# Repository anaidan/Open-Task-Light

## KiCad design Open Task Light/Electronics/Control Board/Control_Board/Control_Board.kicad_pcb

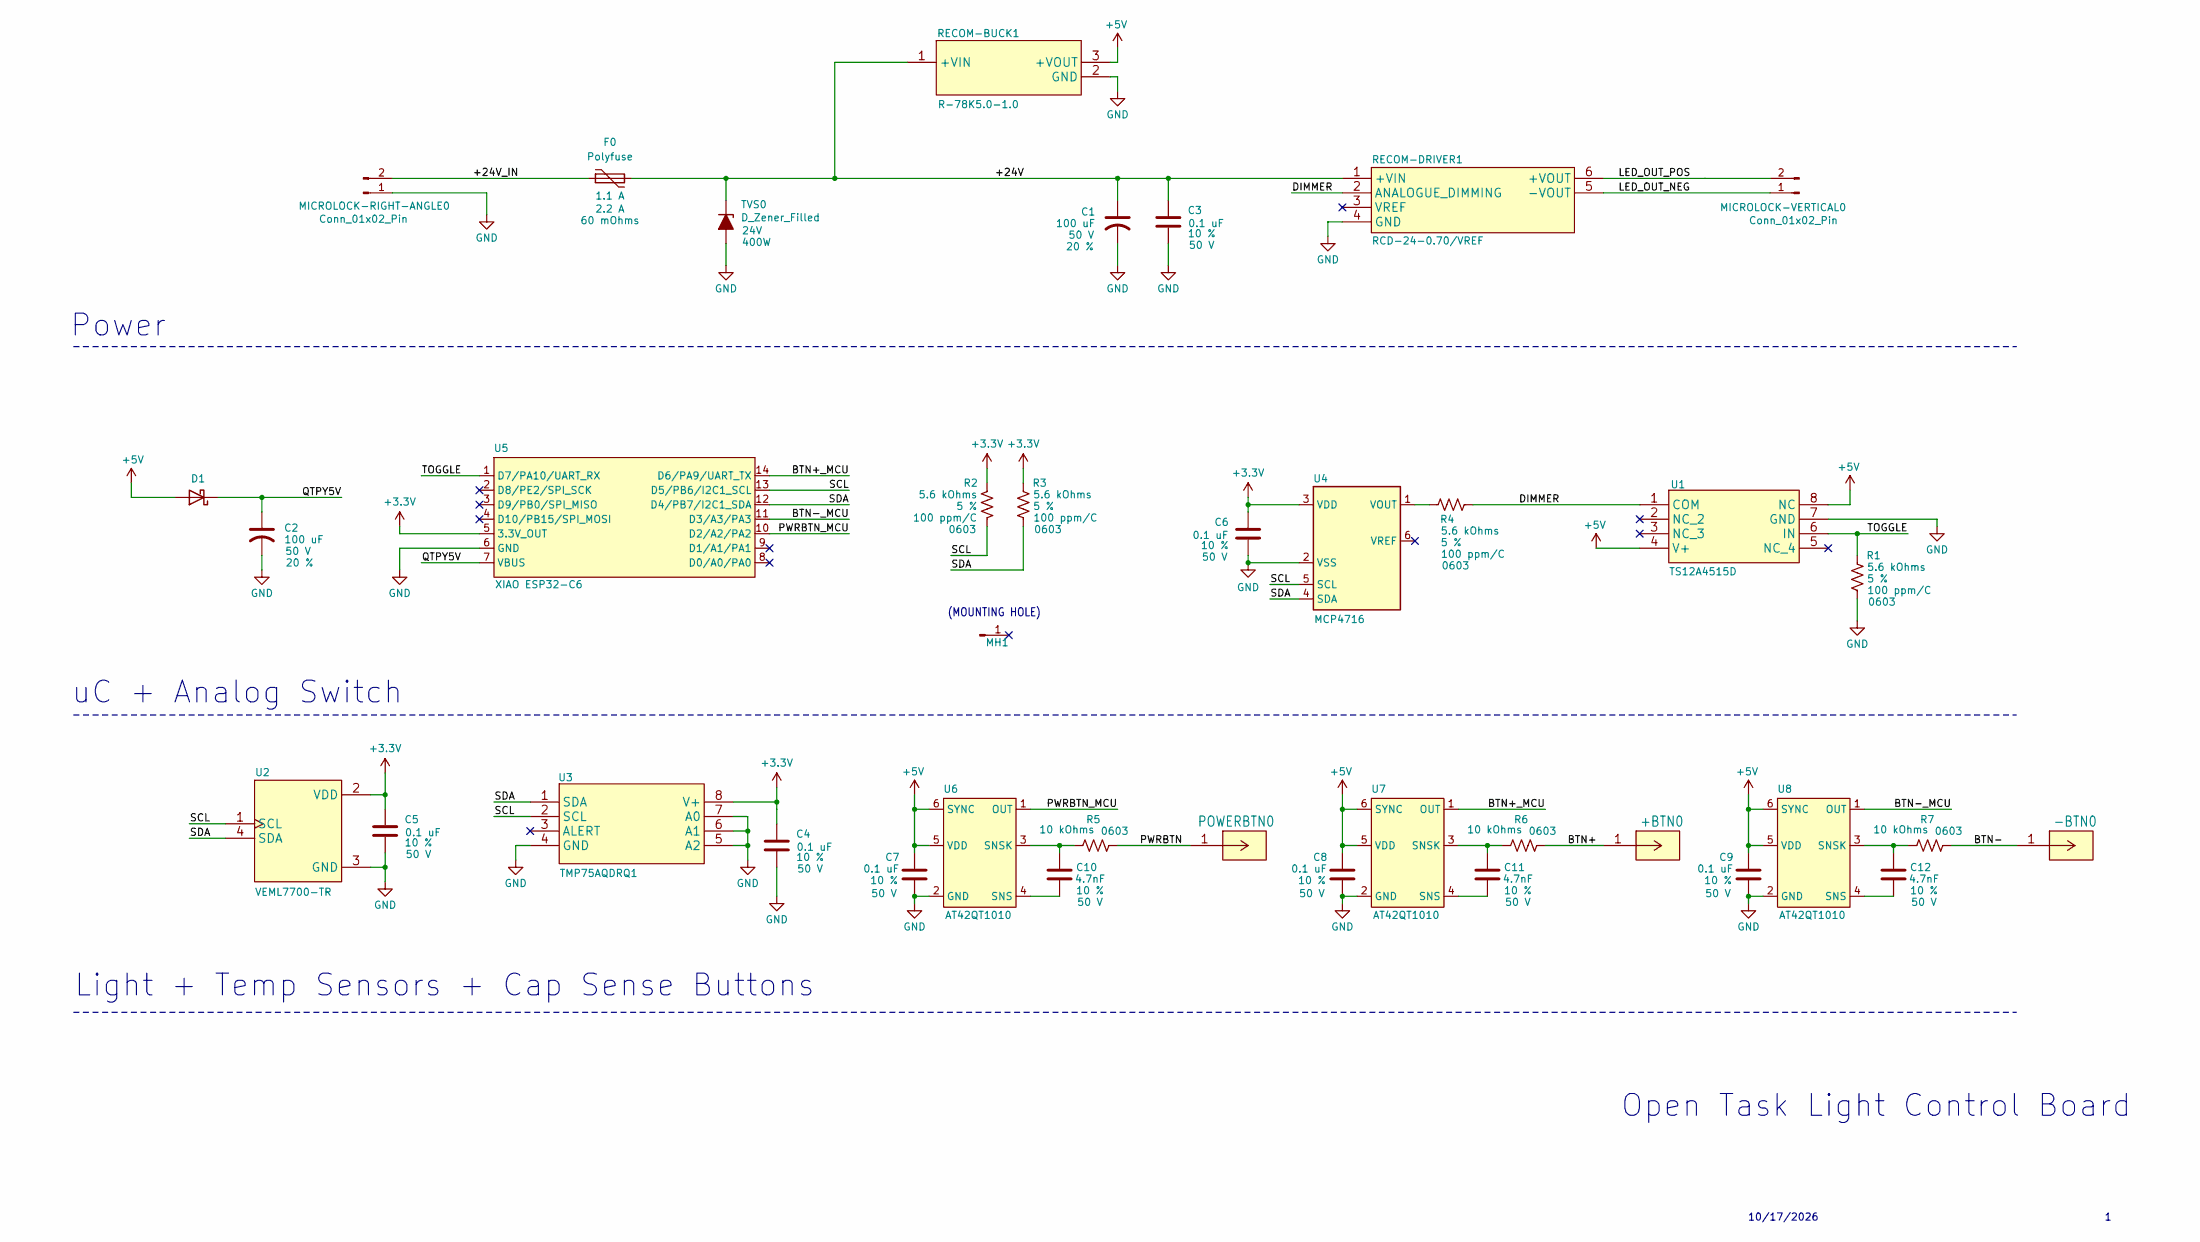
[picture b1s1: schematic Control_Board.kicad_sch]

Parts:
+BTN0: 807-22-001-10-001101; CONN_807-22-001-10-001101_MIM; MPN 807-22-001-10-001101
-BTN0: 807-22-001-10-001101; CONN_807-22-001-10-001101_MIM; MPN 807-22-001-10-001101
C1, C2: EEE-FTH101XAP; CAP_EEEFTH101XAP; Volage Rating 50 V; Tolerance 20 %; MPN EEE-FTH101XAP
C3, C4, C5, C6, C7, C8, C9: C; C_0603_1608Metric; Voltage Rating 50 V; Tolerance 10 %; MPN C0603C104K5RAC9109
C10, C11, C12: C; C_0603_1608Metric; Voltage Rating 50 V; Tolerance 10 %; MPN C0603C472K5RACTU
D1: 1N5819HW-7-F; D_SOD-123; MPN 1N5819HW-7-F
F0: Polyfuse; SMD2016B100TF_33; MPN SMD2016B100TF/33
MH1: 2.5MMPLATEDTHROUGHHOLE; 2.5MMPLATEDHOLE
MICROLOCK-RIGHT-ANGLE0: Conn_01x02_Pin; 2200980271; MPN 2200980271
MICROLOCK-VERTICAL0: Conn_01x02_Pin; 2200970000_A; MPN 2200970271
POWERBTN0: 807-22-001-10-001101; CONN_807-22-001-10-001101_MIM; MPN 807-22-001-10-001101
R1, R2, R3, R4: R_US; R_0603_1608Metric; Tolerance 5 %; MPN AC0603JR-075K6L
R5, R6, R7: R_US; R_0603_1608Metric; Tolerance 5 %; MPN RC0603JR-0710KL
RECOM-BUCK1: R-78K5.0-1.0; R-78K5.0-1.0_RCP; MPN R-78K5.0-1.0
RECOM-DRIVER1: RCD-24-0.70/VREF; RCD24030; MPN RCD-24-0.70/Vref
TVS0: D_Zener_Filled; SODFL3619X98N; MPN SMF4L24AT1G
U1: TS12A4515D; D8-L; MPN TS12A4515D
U2: VEML7700-TR; XDCR_VEML7700-TR; MPN VEML7700-TR
U3: TMP75AQDRQ1; D8_TEX; MPN TMP75AQDRQ1
U4: MCP4716; SOT-23-6; MPN MCP4716A3T-E/CH
U5: XIAO ESP32-C6; ESP32_C6; MPN 113991254
U6, U7, U8: AT42QT1010; SOT-23-6; MPN AT42QT1010-TSHR

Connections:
+3.3V: C4.1, C5.1, C6.1, R2.1, R3.1, U2.2 (VDD), U3.8 (V+), U4.3 (VDD), U5.5 (3.3V_OUT)
+5V: C7.1, C8.1, C9.1, D1.2 (A), RECOM-BUCK1.3 (+VOUT), U1.4 (V+), U1.8 (NC), U6.5 (VDD), U6.6 (SYNC), U7.5 (VDD), U7.6 (SYNC), U8.5 (VDD), U8.6 (SYNC)
/+24V: C1.1, C3.1, F0.2, RECOM-BUCK1.1 (+VIN), RECOM-DRIVER1.1 (+VIN), TVS0.1 (K)
/+24V_IN: F0.1, MICROLOCK-RIGHT-ANGLE0.2
/BTN+: +BTN0.1 (1_1), R6.2
/BTN+_MCU: U5.14 (D6/PA9/UART_TX), U7.1 (OUT)
/BTN-: -BTN0.1 (1_1), R7.2
/BTN-_MCU: U5.11 (D3/A3/PA3), U8.1 (OUT)
/DIMMER: R4.2, RECOM-DRIVER1.2 (ANALOGUE_DIMMING), U1.1 (COM)
/LED_OUT_NEG: MICROLOCK-VERTICAL0.1, RECOM-DRIVER1.5 (-VOUT)
/LED_OUT_POS: MICROLOCK-VERTICAL0.2, RECOM-DRIVER1.6 (+VOUT)
/PWRBTN: POWERBTN0.1 (1_1), R5.2
/PWRBTN_MCU: U5.10 (D2/A2/PA2), U6.1 (OUT)
/QTPY5V: C2.1, D1.1 (K), U5.7 (VBUS)
/SCL: R2.2, U2.1 (SCL), U3.2 (SCL), U4.5 (SCL), U5.13 (D5/PB6/I2C1_SCL)
/SDA: R3.2, U2.4 (SDA), U3.1 (SDA), U4.4 (SDA), U5.12 (D4/PB7/I2C1_SDA)
/TOGGLE: R1.1, U1.6 (IN), U5.1 (D7/PA10/UART_RX)
GND: C1.2, C2.2, C3.2, C4.2, C5.2, C6.2, C7.2, C8.2, C9.2, MICROLOCK-RIGHT-ANGLE0.1, R1.2, RECOM-BUCK1.2 (GND), RECOM-DRIVER1.4 (GND), TVS0.2 (A), U1.7 (GND), U2.3 (GND), U3.4 (GND), U3.5 (A2), U3.6 (A1), U3.7 (A0), U4.2 (VSS), U5.6 (GND), U6.2 (GND), U7.2 (GND), U8.2 (GND)
unnamed: R4.1, U4.1 (VOUT)
unnamed: C10.2, U6.4 (SNS)
unnamed: C10.1, R5.1, U6.3 (SNSK)
unnamed: C11.2, U7.4 (SNS)
unnamed: C11.1, R6.1, U7.3 (SNSK)
unnamed: C12.2, U8.4 (SNS)
unnamed: C12.1, R7.1, U8.3 (SNSK)

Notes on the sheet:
uC + Analog Switch
Power
Open Task Light Control Board
Light + Temp Sensors + Cap Sense Buttons
(MOUNTING HOLE)
10/17/2026

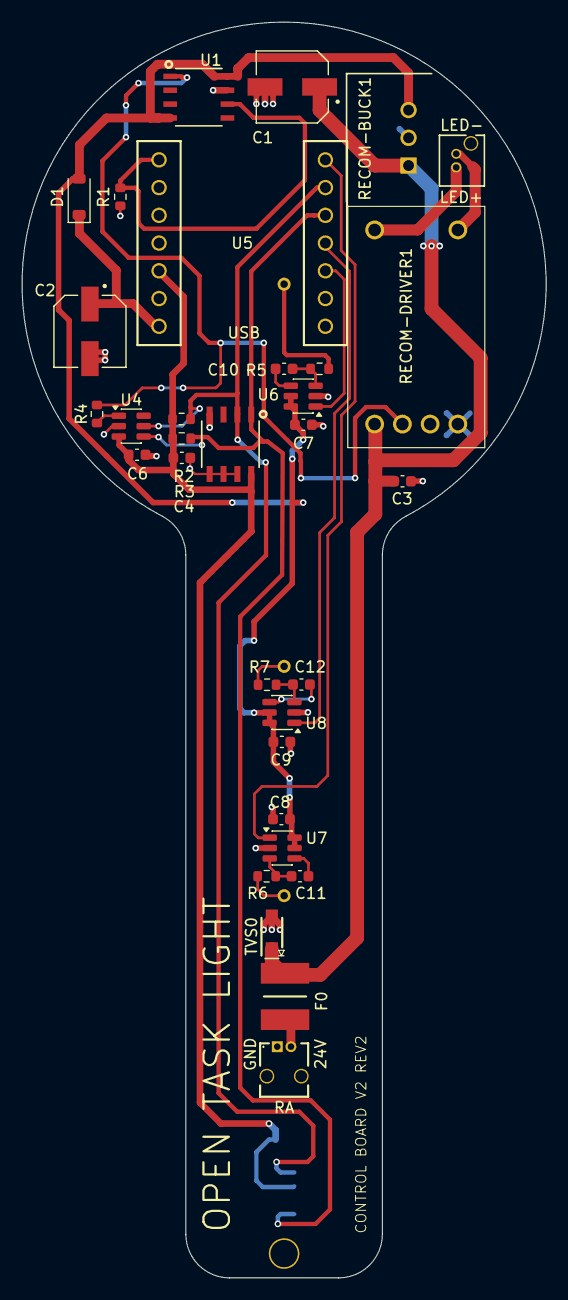
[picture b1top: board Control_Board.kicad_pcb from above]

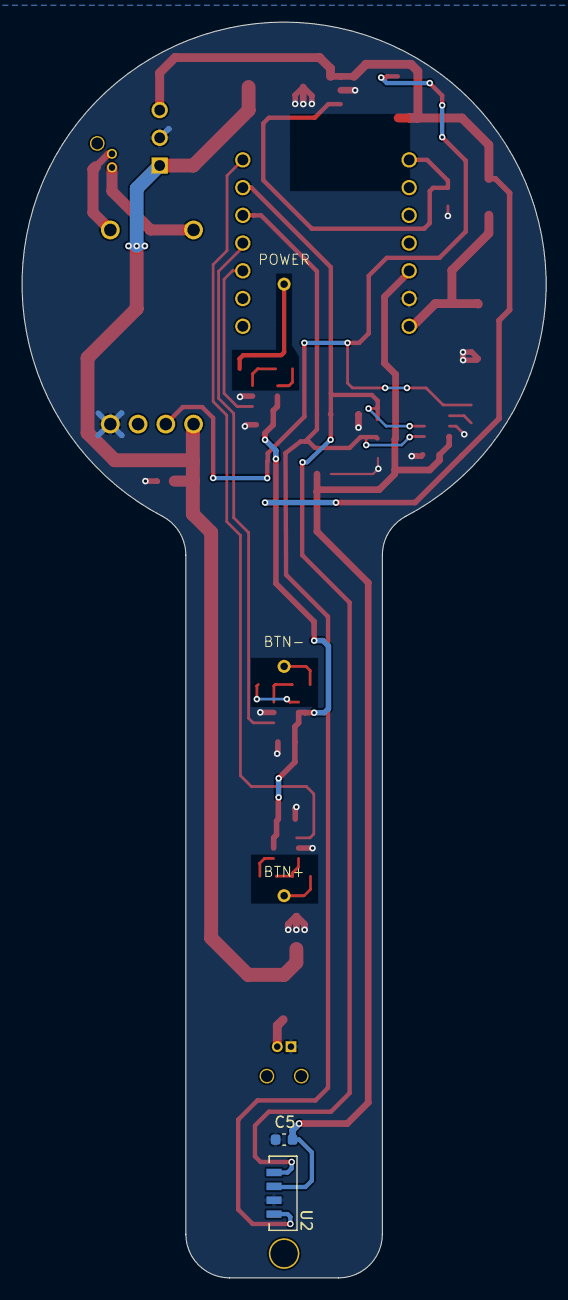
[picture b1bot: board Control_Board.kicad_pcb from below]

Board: 2 copper layers, 48.0 x 115.0 mm, 38 parts (5 on the bottom side), 25 nets.
